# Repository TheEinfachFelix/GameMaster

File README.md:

# GameMaster
A Framework that alows you to easely program gameshows

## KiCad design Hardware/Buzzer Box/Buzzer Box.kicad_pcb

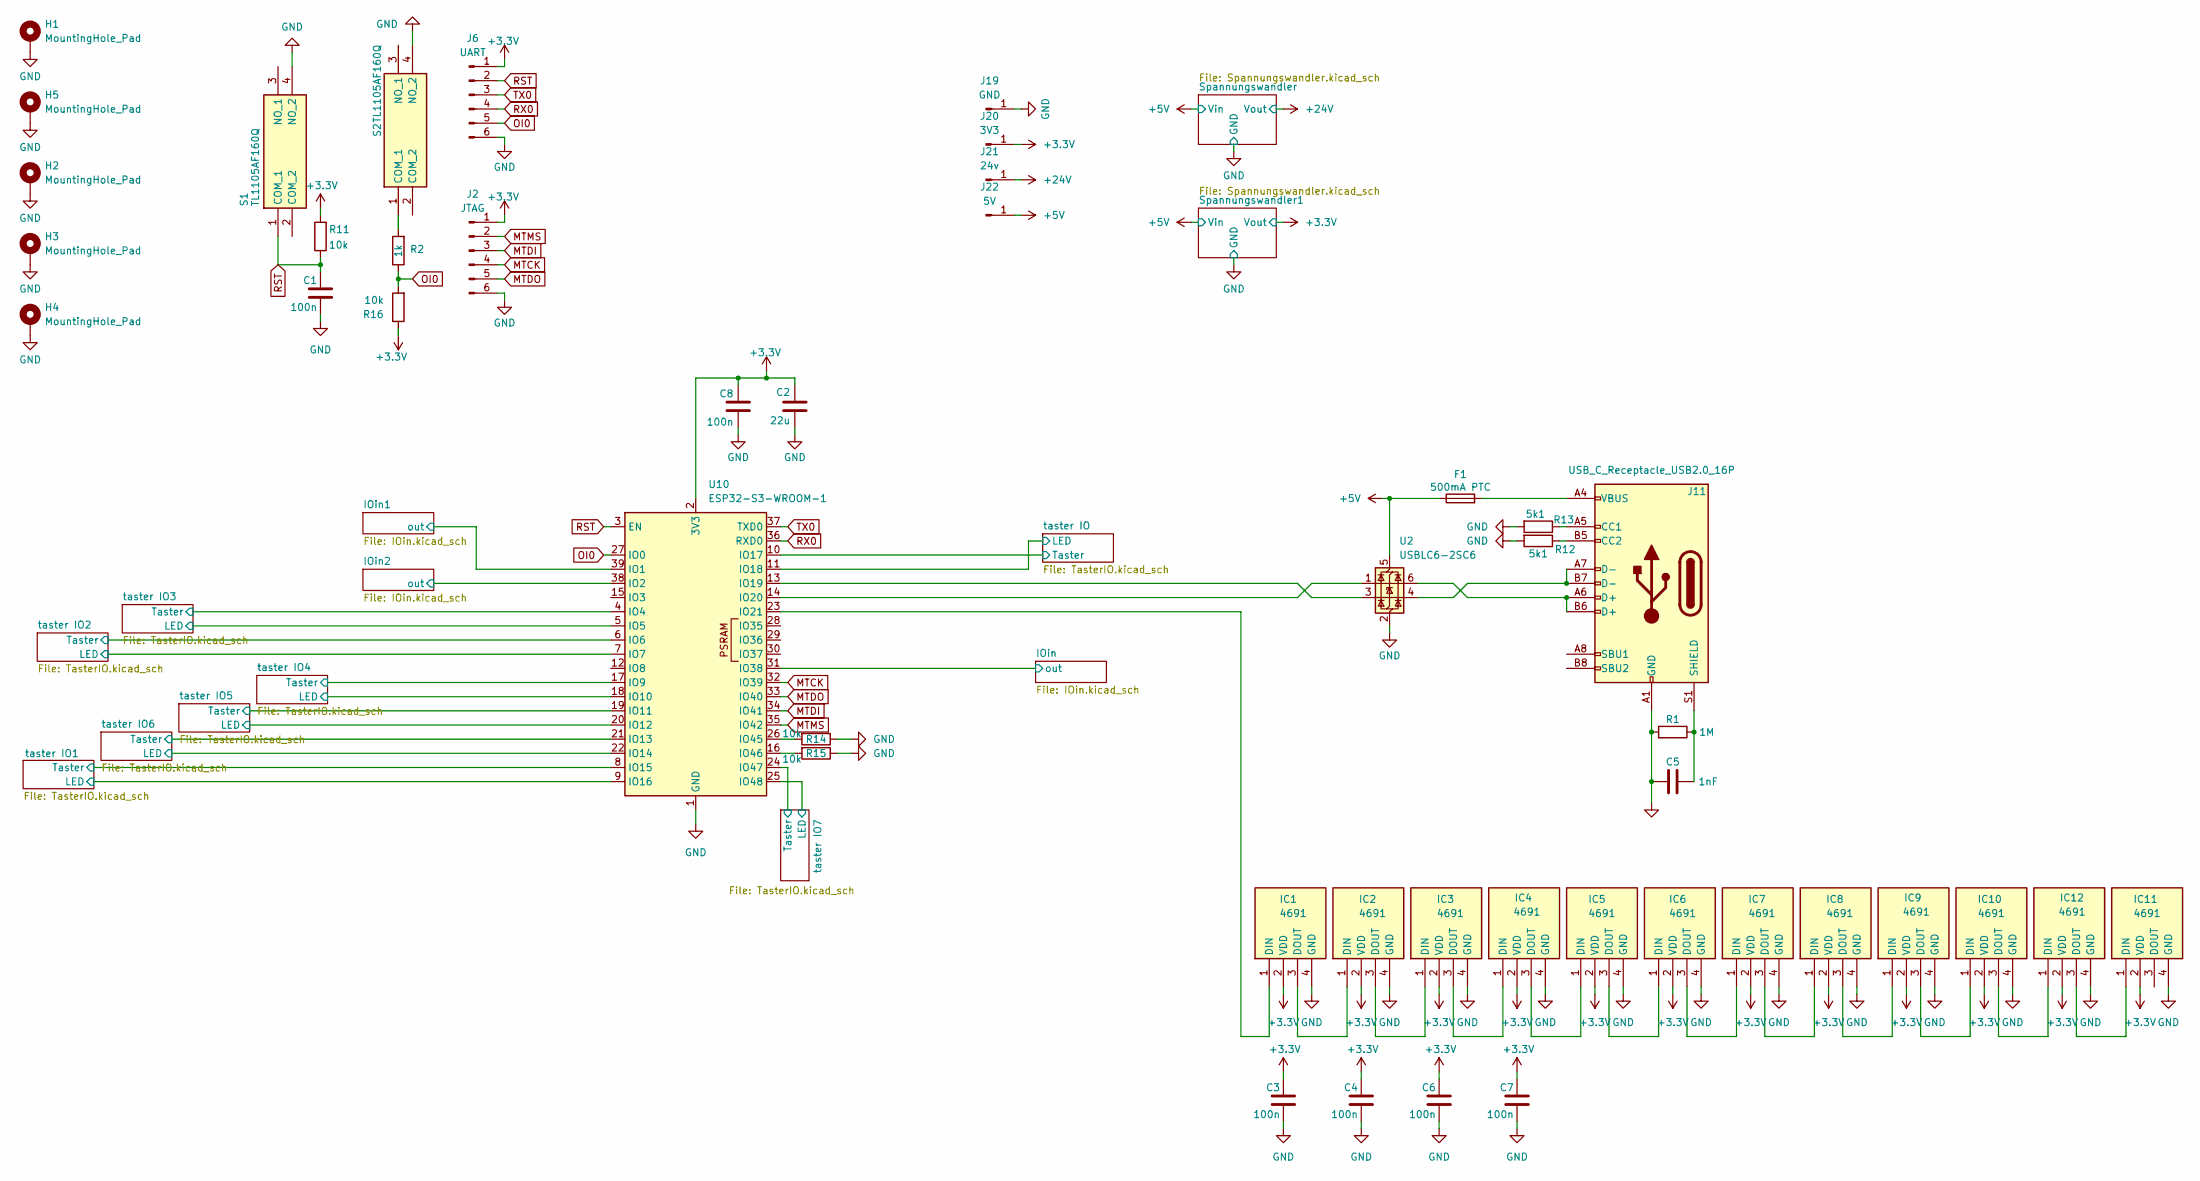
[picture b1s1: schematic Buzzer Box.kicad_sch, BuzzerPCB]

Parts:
C1, C3, C4, C6, C7, C8: 100n; C_0603_1608Metric
C2: 22u; C_0603_1608Metric
C5: 1nF; C_1206_3216Metric
F1: 500mA PTC; Fuse_1206_3216Metric_Pad1.42x1.75mm_HandSolder
H1, H2, H3, H4, H5: MountingHole_Pad; MountingHole_3.2mm_M3_ISO14580_Pad_TopBottom
IC1, IC2, IC3, IC4, IC5, IC6, IC7, IC8, IC9, IC10, IC11, IC12: 4691; Mouser Part Number 485-4691
J2: JTAG; 490107670612
J6: UART; 490107670612
J11: USB_C_Receptacle_USB2.0_16P; USB_C_Receptacle_HRO_TYPE-C-31-M-12
J19: GND; SolderWirePad_1x01_SMD_1x2mm
J20: 3V3; SolderWirePad_1x01_SMD_1x2mm
J21: 24v; SolderWirePad_1x01_SMD_1x2mm
J22: 5V; SolderWirePad_1x01_SMD_1x2mm
R1: 1M; R_1206_3216Metric
R2: 1k; R_0603_1608Metric
R11, R14, R15, R16: 10k; R_0603_1608Metric
R12, R13: 5k1; R_1206_3216Metric
S1, S2: TL1105AF160Q; Mouser Part Number 612-TL1105A
U2: USBLC6-2SC6; SOT-23-6
U10: ESP32-S3-WROOM-1

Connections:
+3.3V: C2.2, C3.2, C4.2, C6.2, C7.2, C8.2, IC1.2 (VDD), IC2.2 (VDD), IC3.2 (VDD), IC4.2 (VDD), IC5.2 (VDD), IC6.2 (VDD), IC7.2 (VDD), IC8.2 (VDD), IC9.2 (VDD), IC10.2 (VDD), IC11.2 (VDD), IC12.2 (VDD), J2.1, J6.1, J20.1, R11.2, R16.1, U10.2 (3V3); also elsewhere on the board
+5V: F1.1, J22.1, U2.5 (VBUS); also elsewhere on the board
+24V: J21.1; also elsewhere on the board
/IOin1/out: U10.39 (IO1); also elsewhere on the board
/IOin2/out: U10.38 (IO2); also elsewhere on the board
/IOin/out: U10.31 (IO38); also elsewhere on the board
/taster IO1/LED: U10.9 (IO16); also elsewhere on the board
/taster IO1/Taster: U10.8 (IO15); also elsewhere on the board
/taster IO2/LED: U10.7 (IO7); also elsewhere on the board
/taster IO2/Taster: U10.6 (IO6); also elsewhere on the board
/taster IO3/LED: U10.5 (IO5); also elsewhere on the board
/taster IO3/Taster: U10.4 (IO4); also elsewhere on the board
/taster IO4/LED: U10.18 (IO10); also elsewhere on the board
/taster IO4/Taster: U10.17 (IO9); also elsewhere on the board
/taster IO5/LED: U10.20 (IO12); also elsewhere on the board
/taster IO5/Taster: U10.19 (IO11); also elsewhere on the board
/taster IO6/LED: U10.22 (IO14); also elsewhere on the board
/taster IO6/Taster: U10.21 (IO13); also elsewhere on the board
/taster IO7/LED: U10.25 (IO48); also elsewhere on the board
/taster IO7/Taster: U10.24 (IO47); also elsewhere on the board
/taster IO/LED: U10.11 (IO18); also elsewhere on the board
/taster IO/Taster: U10.10 (IO17); also elsewhere on the board
GND: C1.1, C2.1, C3.1, C4.1, C5.2, C6.1, C7.1, C8.1, H1.1, H2.1, H3.1, H4.1, H5.1, IC1.4 (GND), IC2.4 (GND), IC3.4 (GND), IC4.4 (GND), IC5.4 (GND), IC6.4 (GND), IC7.4 (GND), IC8.4 (GND), IC9.4 (GND), IC10.4 (GND), IC11.4 (GND), IC12.4 (GND), J2.6, J6.6, J11.A1 (GND), J11.A12 (GND), J11.B1 (GND), J11.B12 (GND), J19.1, R1.2, R12.2, R13.2, R14.1, R15.1, S1.4 (NO_2), S2.4 (NO_2), U2.2 (GND), U10.1 (GND), U10.40 (GND), U10.41 (GND); also elsewhere on the board
MTCK: J2.4, U10.32 (IO39)
MTDI: J2.3, U10.34 (IO41)
MTDO: J2.5, U10.33 (IO40)
MTMS: J2.2, U10.35 (IO42)
unnamed: F1.2, J11.A4 (VBUS), J11.A9 (VBUS), J11.B4 (VBUS), J11.B9 (VBUS)
unnamed: IC1.1 (DIN), U10.23 (IO21)
unnamed: IC1.3 (DOUT), IC2.1 (DIN)
unnamed: IC2.3 (DOUT), IC3.1 (DIN)
unnamed: IC3.3 (DOUT), IC4.1 (DIN)
unnamed: IC4.3 (DOUT), IC5.1 (DIN)
unnamed: IC5.3 (DOUT), IC6.1 (DIN)
unnamed: IC6.3 (DOUT), IC7.1 (DIN)
unnamed: IC7.3 (DOUT), IC8.1 (DIN)
unnamed: IC8.3 (DOUT), IC9.1 (DIN)
unnamed: IC9.3 (DOUT), IC10.1 (DIN)
unnamed: IC10.3 (DOUT), IC12.1 (DIN)
unnamed: IC11.1 (DIN), IC12.3 (DOUT)
unnamed: J11.A5 (CC1), R13.1
unnamed: J11.B5 (CC2), R12.1
unnamed: J11.A6 (D+), J11.B6 (D+), U2.6 (I/O1)
unnamed: J11.A7 (D-), J11.B7 (D-), U2.4 (I/O2)
unnamed: C5.1, J11.S1 (SHIELD), R1.1
unnamed: R2.2, S2.1 (COM_1)
unnamed: U2.3 (I/O2), U10.13 (IO19)
unnamed: U2.1 (I/O1), U10.14 (IO20)
unnamed: R14.2, U10.26 (IO45)
unnamed: R15.2, U10.16 (IO46)
OI0: J6.5, R2.1, R16.2, U10.27 (IO0)
RST: C1.2, J6.2, R11.1, S1.1 (COM_1), U10.3 (EN)
RX0: J6.4, U10.36 (RXD0)
TX0: J6.3, U10.37 (TXD0)

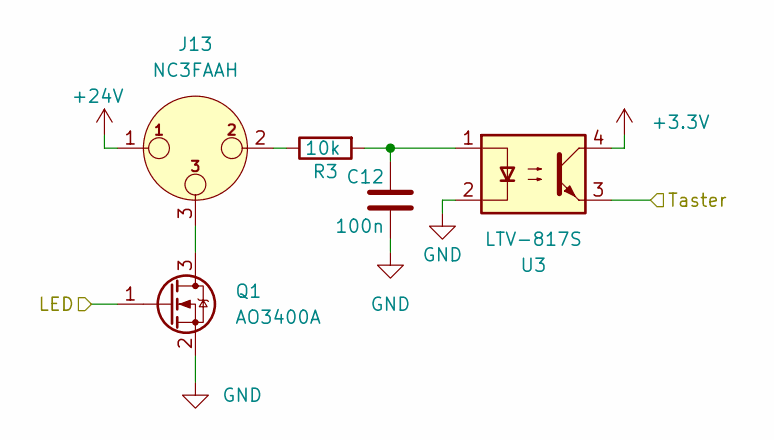
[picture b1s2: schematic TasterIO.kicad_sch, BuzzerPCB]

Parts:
C12: 100n; C_0603_1608Metric
J13: NC3FAAH; Jack_XLR_Neutrik_NC3FAAH_Horizontal
Q1: AO3400A; SOT-23
R3: 10k; R_0603_1608Metric
U3: LTV-817S; SMDIP-4_W9.53mm

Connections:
+3.3V: U3.4; also elsewhere on the board
+24V: J13.1; also elsewhere on the board
/taster IO/LED: Q1.1 (G); also elsewhere on the board
/taster IO/Taster: U3.3; also elsewhere on the board
GND: C12.1, Q1.2 (S), U3.2; also elsewhere on the board
unnamed: C12.2, R3.2, U3.1
unnamed: J13.2, R3.1
unnamed: J13.3, Q1.3 (D)

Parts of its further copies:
C13, C14, C15, C16, C17, C18, C19: 100n; C_0603_1608Metric
J14, J17, J18, J23, J24, J25, J26: NC3FAAH; Jack_XLR_Neutrik_NC3FAAH_Horizontal
Q2, Q3, Q4, Q5, Q6, Q7, Q8: AO3400A; SOT-23
R4, R5, R6, R7, R8, R9, R10: 10k; R_0603_1608Metric
U1, U4, U5, U6, U7, U8, U9: LTV-817S; SMDIP-4_W9.53mm

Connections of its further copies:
+3.3V: U1.4, U4.4, U5.4, U6.4, U7.4, U8.4, U9.4; also elsewhere on the board
+24V: J14.1, J17.1, J18.1, J23.1, J24.1, J25.1, J26.1; also elsewhere on the board
/taster IO1/LED: Q2.1 (G); also elsewhere on the board
/taster IO1/Taster: U1.3; also elsewhere on the board
/taster IO2/LED: Q3.1 (G); also elsewhere on the board
/taster IO2/Taster: U4.3; also elsewhere on the board
/taster IO3/LED: Q4.1 (G); also elsewhere on the board
/taster IO3/Taster: U5.3; also elsewhere on the board
/taster IO4/LED: Q5.1 (G); also elsewhere on the board
/taster IO4/Taster: U6.3; also elsewhere on the board
/taster IO5/LED: Q6.1 (G); also elsewhere on the board
/taster IO5/Taster: U7.3; also elsewhere on the board
/taster IO6/LED: Q7.1 (G); also elsewhere on the board
/taster IO6/Taster: U8.3; also elsewhere on the board
/taster IO7/LED: Q8.1 (G); also elsewhere on the board
/taster IO7/Taster: U9.3; also elsewhere on the board
GND: C13.1, C14.1, C15.1, C16.1, C17.1, C18.1, C19.1, Q2.2 (S), Q3.2 (S), Q4.2 (S), Q5.2 (S), Q6.2 (S), Q7.2 (S), Q8.2 (S), U1.2, U4.2, U5.2, U6.2, U7.2, U8.2, U9.2; also elsewhere on the board
unnamed: C13.2, R4.2, U1.1
unnamed: C14.2, R5.2, U4.1
unnamed: C15.2, R6.2, U5.1
unnamed: C16.2, R7.2, U6.1
unnamed: C17.2, R8.2, U7.1
unnamed: C18.2, R9.2, U8.1
unnamed: C19.2, R10.2, U9.1
unnamed: J14.2, R4.1
unnamed: J17.2, R5.1
unnamed: J18.2, R6.1
unnamed: J23.2, R7.1
unnamed: J24.2, R8.1
unnamed: J25.2, R9.1
unnamed: J26.2, R10.1
unnamed: J14.3, Q2.3 (D)
unnamed: J17.3, Q3.3 (D)
unnamed: J18.3, Q4.3 (D)
unnamed: J23.3, Q5.3 (D)
unnamed: J24.3, Q6.3 (D)
unnamed: J25.3, Q7.3 (D)
unnamed: J26.3, Q8.3 (D)

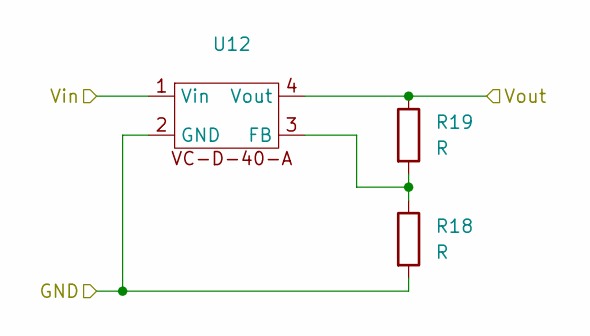
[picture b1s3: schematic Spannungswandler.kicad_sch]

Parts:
R18, R19: R; R_0805_2012Metric_Pad1.20x1.40mm_HandSolder
U12: VC-D-40-A

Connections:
+3.3V: R19.1, U12.4 (Vout); also elsewhere on the board
+5V: U12.1 (Vin); also elsewhere on the board
GND: R18.2, U12.2 (GND); also elsewhere on the board

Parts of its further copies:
R17, R20: R; R_0805_2012Metric_Pad1.20x1.40mm_HandSolder
U11: VC-D-40-A

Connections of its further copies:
+5V: U11.1 (Vin); also elsewhere on the board
+24V: R17.1, U11.4 (Vout); also elsewhere on the board
GND: R20.2, U11.2 (GND); also elsewhere on the board

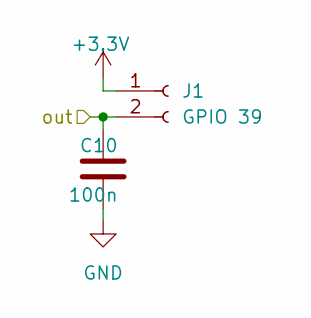
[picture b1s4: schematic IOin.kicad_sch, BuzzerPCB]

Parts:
C10: 100n; C_0603_1608Metric
J1: GPIO 39; JST_XH_B2B-XH-A_1x02_P2.50mm_Vertical

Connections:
+3.3V: J1.1; also elsewhere on the board
/IOin/out: C10.2, J1.2; also elsewhere on the board
GND: C10.1; also elsewhere on the board

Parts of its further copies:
C9, C11: 100n; C_0603_1608Metric
J4, J5: GPIO 39; JST_XH_B2B-XH-A_1x02_P2.50mm_Vertical

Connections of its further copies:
+3.3V: J4.1, J5.1; also elsewhere on the board
/IOin1/out: C9.2, J4.2; also elsewhere on the board
/IOin2/out: C11.2, J5.2; also elsewhere on the board
GND: C9.1, C11.1; also elsewhere on the board

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
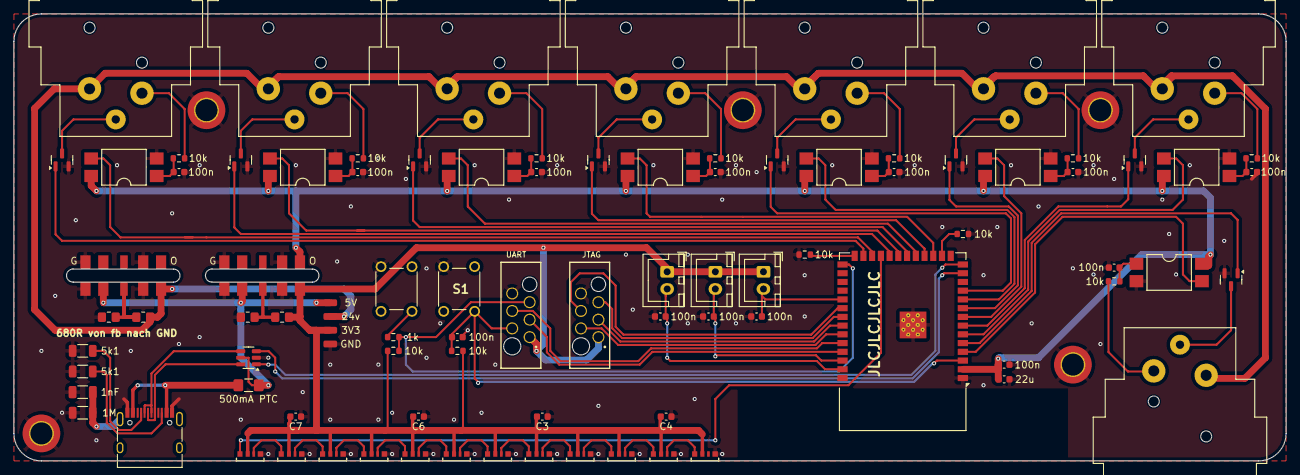
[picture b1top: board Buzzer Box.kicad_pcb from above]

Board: 2 copper layers, 185.0 x 65.0 mm, 97 parts (0 on the bottom side), 80 nets.

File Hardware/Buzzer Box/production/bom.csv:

Designator,Footprint,Quantity,Value,LCSC Part #
"C1, C10, C11, C12, C13, C14, C15, C16, C17, C18, C19, C3, C4, C6, C7, C8, C9",0603,17,100n,
C2,0603,1,22u,
C5,1206,1,1nF,
F1,1206,1,500mA PTC,
"IC1, IC10, IC11, IC12, IC2, IC3, IC4, IC5, IC6, IC7, IC8, IC9",4691,12,4691,
"J1, J4, J5",JST_XH_B2B-XH-A_1x02_P2.50mm_Vertical,3,GPIO 39,
J11,USB_C_Receptacle_HRO_TYPE-C-31-M-12,1,USB_C_Receptacle_USB2.0_16P,
"J13, J14, J17, J18, J23, J24, J25, J26",Jack_XLR_Neutrik_NC3FAAH_Horizontal,8,NC3FAAH,
J19,SolderWirePad_1x01_SMD_1x2mm,1,GND,
J2,490107670612,1,JTAG,
J20,SolderWirePad_1x01_SMD_1x2mm,1,3V3,
J21,SolderWirePad_1x01_SMD_1x2mm,1,24v,
J22,SolderWirePad_1x01_SMD_1x2mm,1,5V,
J6,490107670612,1,UART,
"Q1, Q2, Q3, Q4, Q5, Q6, Q7, Q8",SOT-23,8,AO3400A,
R1,1206,1,1M,
"R10, R11, R14, R15, R16, R3, R4, R5, R6, R7, R8, R9",0603,12,10k,
"R12, R13",1206,2,5k1,
"R17, R18, R19, R20",0805,4,R,
R2,0603,1,1k,
"S1, S2",TL1105AF160Q,2,TL1105AF160Q,
"U1, U3, U4, U5, U6, U7, U8, U9",SMDIP-4_W9.53mm,8,LTV-817S,
U10,ESP32-S3-WROOM-1,1,ESP32-S3-WROOM-1,
"U11, U12",VC-D-40-A,2,~,
U2,SOT-23-6,1,USBLC6-2SC6,

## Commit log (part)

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2024-05-06 made some first brainstorming ideas
2024-05-08 Made some more notes
2024-05-08 wrote some class information
2024-05-08 Added Projekt and added gitignore
2024-05-08 unit tests and more implementation
2024-05-08 setup for buzzer
2024-05-09 wrote buzzer script + more implementations for game
2024-05-09 Buzzer are now working
2024-05-09 updated Doku
2024-05-10 new branch to tackle thfinisched the Auido Playere audio player
2024-05-10 wrote the first implematntation of the dot2 connector
2024-05-12 dot 2 is fully implemented
2024-05-12 created projekt for asp
2024-05-26 some changes
2024-05-27 implemented busser class
2024-05-28 wrote more classes
2024-05-28 bugfixes and now compiling
2024-05-28 fixed upload issue
2024-05-28 Fixed LEDs
2024-05-29 fixed all compiler errors. added taster
2024-05-29 nice formating
2024-05-29 made some changes
2024-05-29 changed a bit
2024-05-29 fixed all bugs now ownly read serial is missing
2024-05-30 Added the Data recieving
2024-05-31 updated times
2024-05-31 mase sme cjangea
2024-06-09 started wpf controoler
2024-06-10 minor hawarde code chage
2024-06-10 started to implement the buzzer handler
2024-06-10 fully implemented the buzzer
2024-06-10 Fixed all the Bugs
2024-06-11 added todo
2024-06-12 controller is now working as mvp
2024-06-15 implemented Obs controll
2024-06-15 updated notes
2024-06-17 added some stuff to the Json
2024-06-17 started the new window
2024-06-20 Removed old files
2024-06-21 marked some todos
2024-06-21 Added a ToDo
2024-06-29 added simul audio playing
2024-06-29 some minor fixes
2024-07-03 stuff
2024-07-03 bug fixes many
2024-07-03 more changes
2024-07-03 time changes
2024-07-03 updated the times
2024-08-17 die verändeerungen im camp
2024-08-17 far better buzzer handling untested
2024-08-18 implemented it forking ok
2024-08-18 updated to do list
2024-08-26 fixed id offset part1
2024-08-26 fixed buzzer id mapping
2024-08-26 fixed taster id offset
2024-08-26 added note do brainstorming
2024-08-26 made a strat to the get requests
2024-08-26 started api design
2024-08-28 Started the Implementation of the new api
2024-08-29 the api implenentation is complet for the esp
2024-08-29 better json creation using serializeJson
2024-08-29 started regex stuff
2024-08-29 added test script
2024-08-29 finished example
2024-08-30 wrote doku and repleced regex and changed request rgb parameter
2024-08-30 added automatic input buffer clearing
2024-08-30 Fixed ESP Api
2024-09-03 reqerote the json handling
2024-09-03 filanized the api chages
2024-09-03 some more chages
2024-09-17 fixes some api bugs but not all
2024-09-17 fixed doku
2024-09-18 made a posible solution for the getData problem
2024-09-18 craeted s posible fix for the getdata problenm
2024-09-18 refactord the c++ part of the code
2024-09-18 some minor changes to the c# side and cleaning
2024-09-20 infermediat comit lots of bug fixes
2024-09-22 last versin where the c# controlls the leds
2024-09-22 intermediate comit restructuresd a lot
2024-09-22 cleaned the code more
2024-09-22 implemented all the chages to the c++ side
2024-09-22 Fixed a Few bugs
2024-09-22 fully implemented the c#side of the api
2024-09-22 updated the doku and lvl
2024-12-08 rm main.hpp
2024-12-08 midiTest
2024-12-14 added esp idf projekt
2024-12-14 save
2024-12-14 made some bug fixes still not working
2024-12-14 small settings change
2024-12-15 mostly working xD
2024-12-17 Midi Tut
2024-12-17 its working jea
2024-12-17 small chages
2024-12-19 cdc write is now working
2024-12-19 eveyting is working ^^
2024-12-19 Removed unnececary test projekts
2024-12-21 implemented some stuff
2024-12-22 Events are now fully working
2024-12-22 Midi Notes are beeing send
2024-12-22 chages
2024-12-22 Updated the PCB
2024-12-23 Neopixel controll worx
2024-12-23 the ledcontroll now has it own task
2024-12-23 leds are done
2024-12-23 made chages to the PCB
2024-12-24 chaged the usb position on pcb
2024-12-25 added debouncing caps
2024-12-25 fixed lable
2024-12-25 final version
2024-12-28 some chages
2025-05-01 fixed design
2025-06-28 fixed io lights
2025-06-28 working now also fixed the runtime
2025-06-29 Upgrade zu .net9
2025-06-29 using obs to play out text
2025-07-01 Started Implementig a 2x2 Question lvl and switched to obs vor visuals
2025-07-30 Stuff Changed
2025-07-30 Worked on the next Game
2025-08-08 post camp
2025-08-20 Added a Game Index
